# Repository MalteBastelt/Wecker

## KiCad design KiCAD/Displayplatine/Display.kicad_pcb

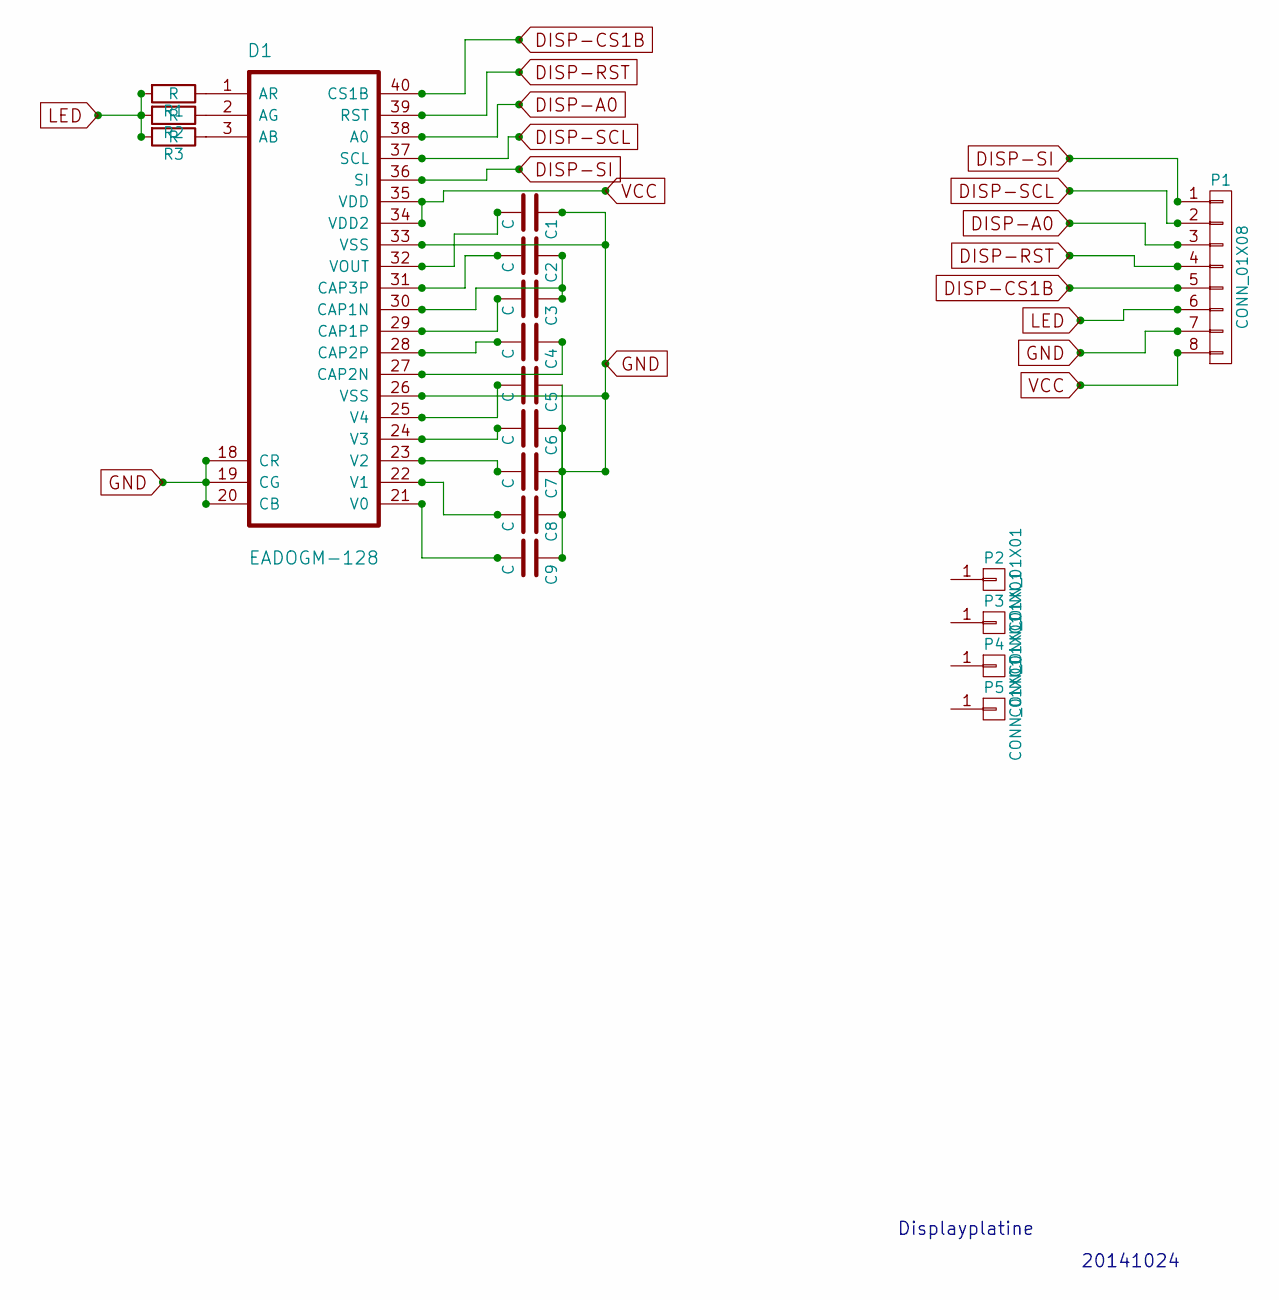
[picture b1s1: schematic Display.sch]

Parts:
C1, C2, C3, C4, C5, C6, C7, C8, C9: C; C_Disc_D7.5_P5
D1: EADOGM-128; EADOG128
P1: CONN_01X08; Pin_Header_Straight_1x08
P2, P3, P4, P5: CONN_01X01; Pin_Header_Straight_1x01
R1, R2, R3: R; Resistor_Horizontal_RM10mm

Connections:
D1: D1.36 (SI), P1.1
D2: D1.37 (SCL), P1.2
D3: D1.38 (A0), P1.3
D4: D1.39 (RST), P1.4
D5: D1.40 (CS1B), P1.5
GND: C1.1, C5.1, C6.1, C7.1, C8.1, C9.1, D1.18 (CR), D1.19 (CG), D1.20 (CB), D1.26 (VSS), D1.33 (VSS), P1.7
LED: P1.6, R1.2, R2.2, R3.2
unnamed: C1.2, D1.32 (VOUT)
unnamed: C2.1, C3.1, D1.30 (CAP1N)
unnamed: C2.2, D1.31 (CAP3P)
unnamed: C3.2, D1.29 (CAP1P)
unnamed: C4.1, D1.27 (CAP2N)
unnamed: C4.2, D1.28 (CAP2P)
unnamed: C5.2, D1.25 (V4)
unnamed: C6.2, D1.24 (V3)
unnamed: C7.2, D1.23 (V2)
unnamed: C8.2, D1.22 (V1)
unnamed: C9.2, D1.21 (V0)
unnamed: D1.1 (AR), R1.1
unnamed: D1.2 (AG), R2.1
unnamed: D1.3 (AB), R3.1
VCC: D1.34 (VDD2), D1.35 (VDD), P1.8

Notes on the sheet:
Displayplatine
20141024

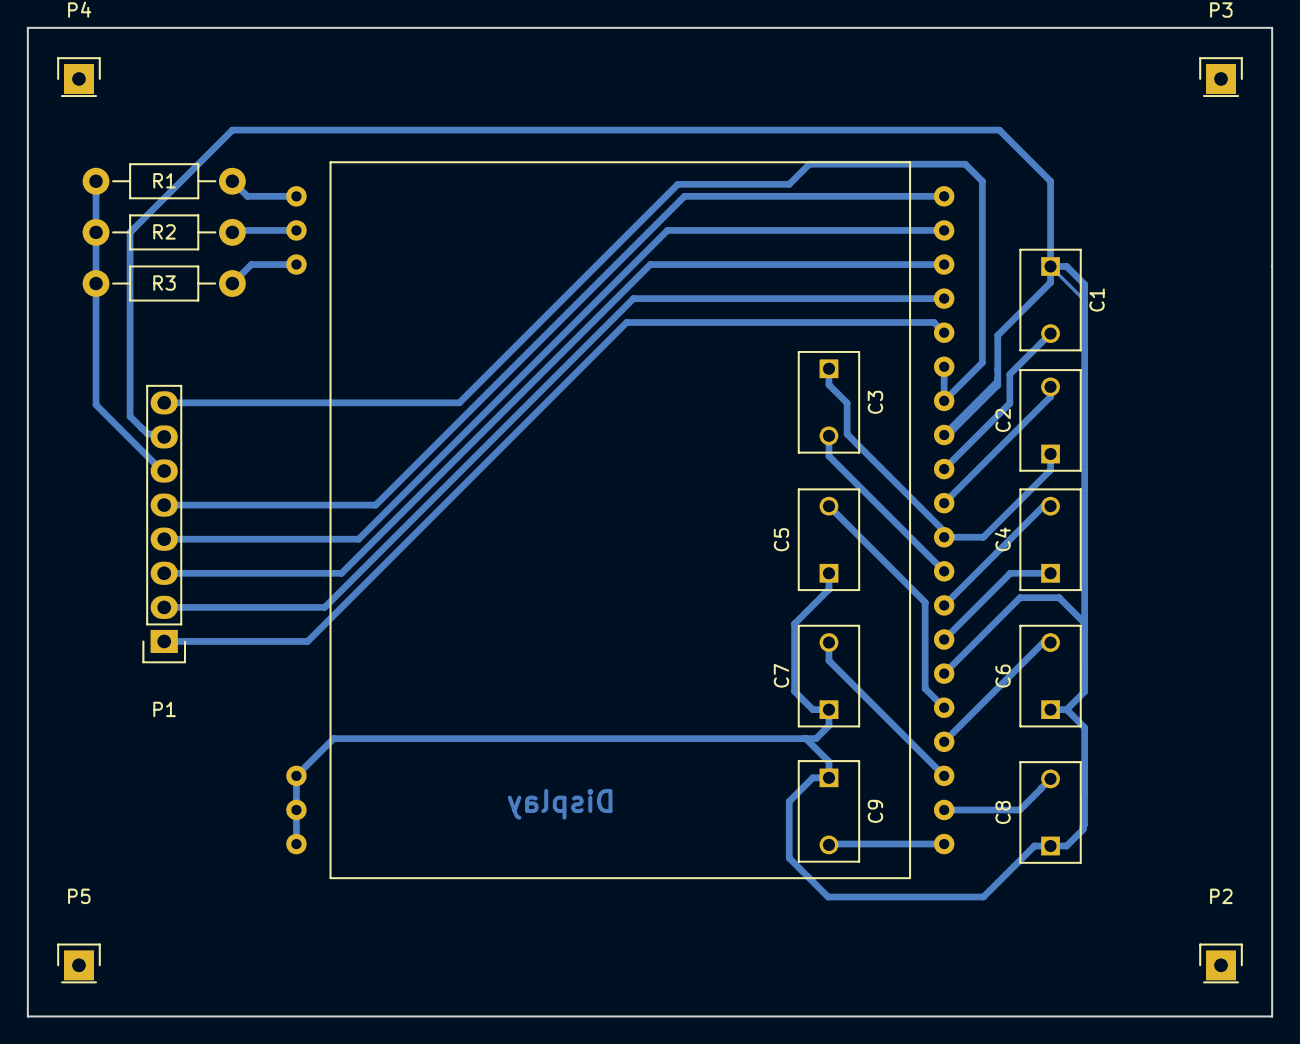
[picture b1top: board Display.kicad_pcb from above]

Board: 2 copper layers, 92.7 x 73.7 mm, 18 parts (0 on the bottom side), 22 nets.

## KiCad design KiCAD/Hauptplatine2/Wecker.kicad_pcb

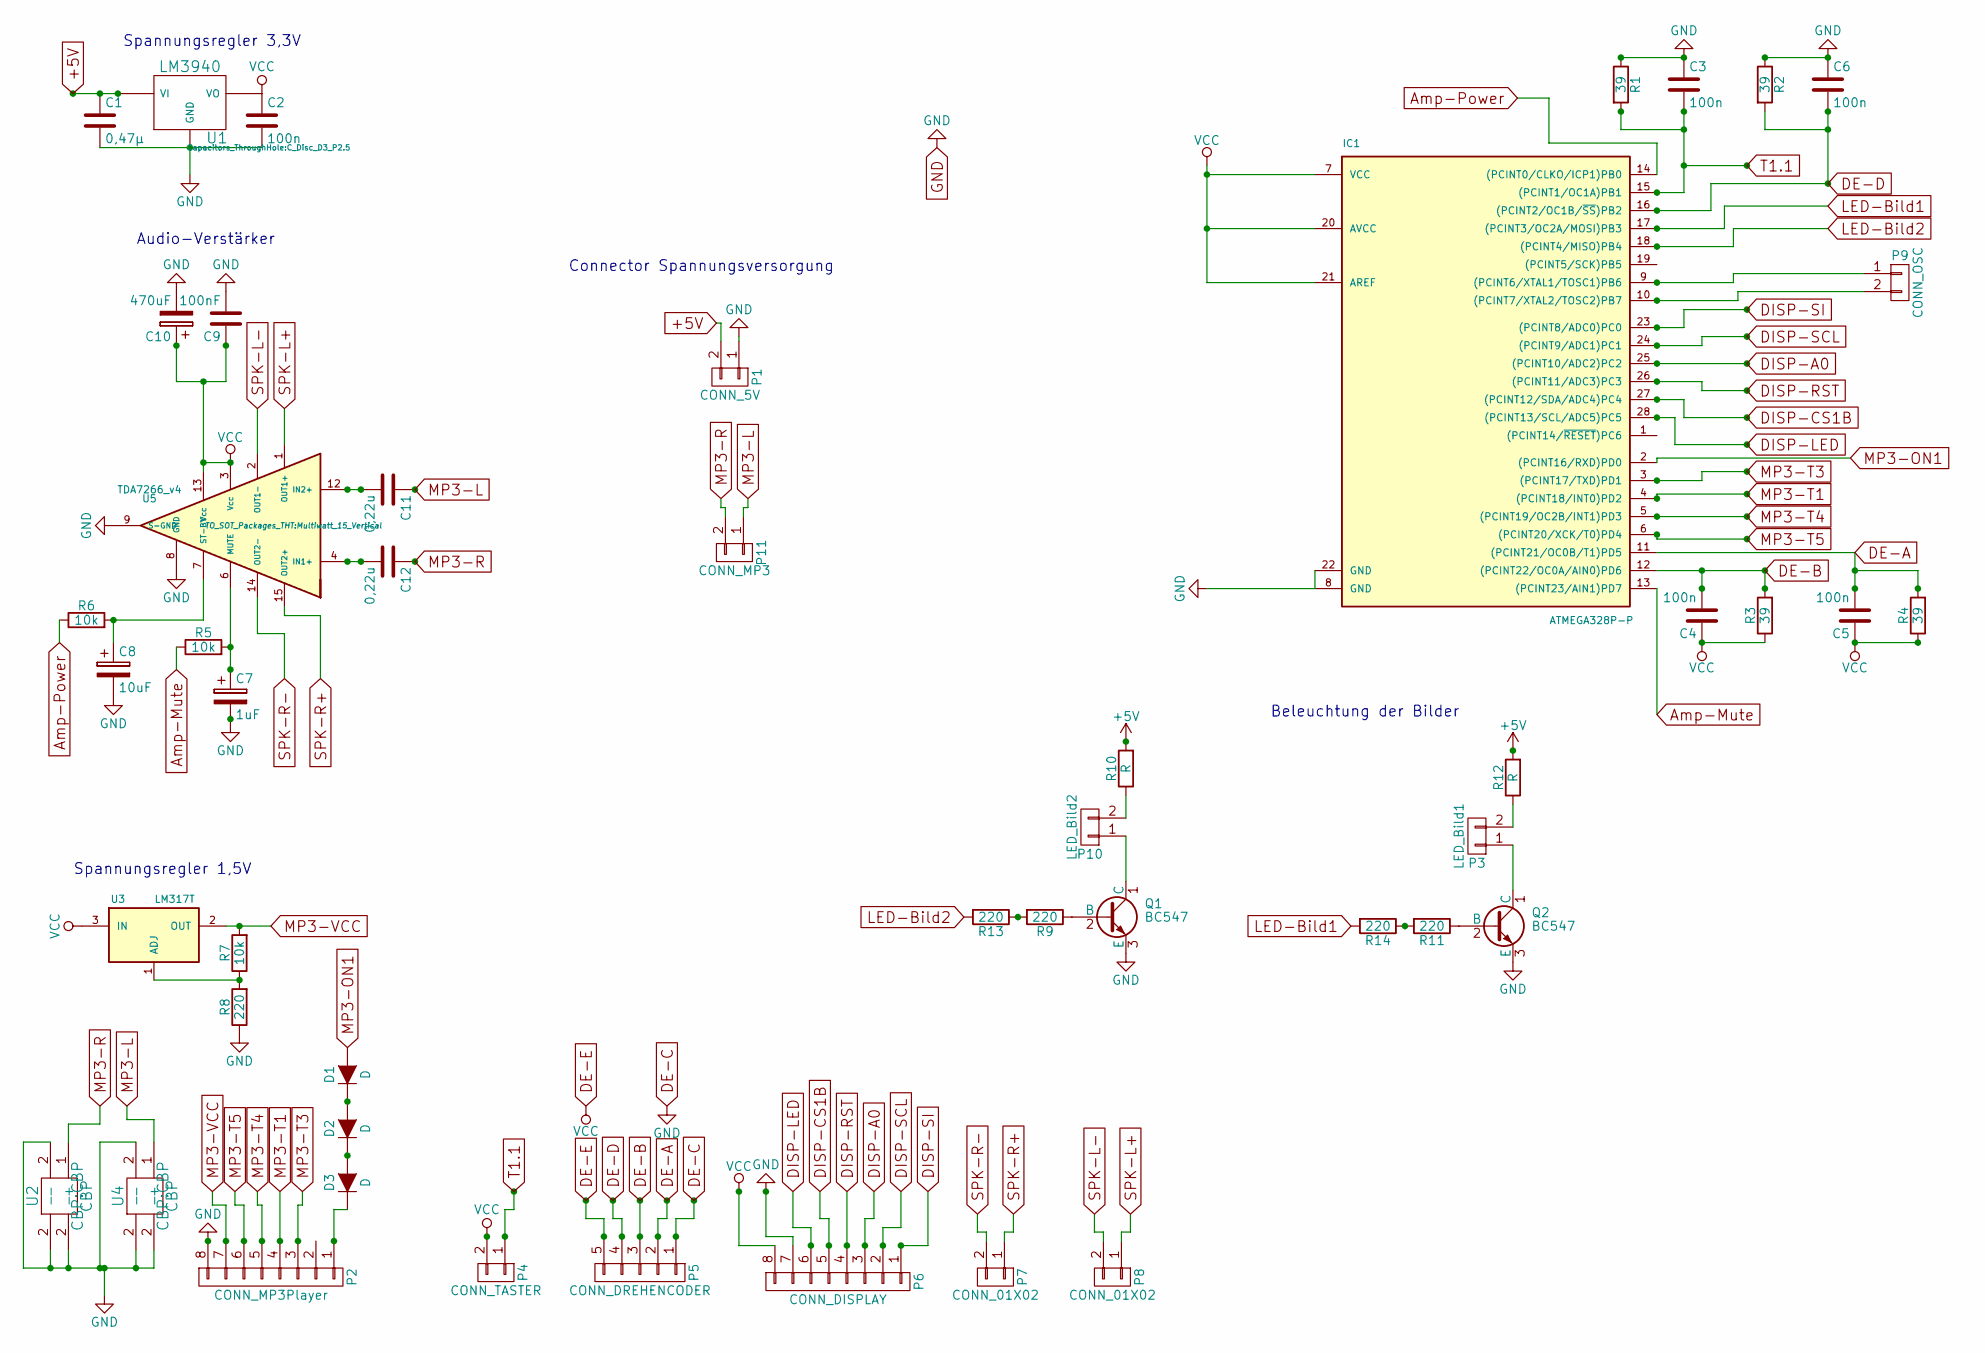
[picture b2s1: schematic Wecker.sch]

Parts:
C1: 0,47µ; C_Disc_D7.5_P5
C2: 100n; C_Disc_D3_P2.5
C3, C4, C5, C6: 100n; C_Disc_D12_P7.75
C7: 1uF; C_Radial_D5_L6_P2.5
C8: 10uF; C_Radial_D5_L6_P2.5
C9: 100nF; C_Disc_D12_P7.75
C10: 470uF; C_Radial_D7.5_L11.2_P2.5
C11, C12: 0,22u; C_Rect_L4_W2.5_P2.5
D1, D2, D3: D; Diode_DO-35_SOD27_Horizontal_RM10
IC1: ATMEGA328P-P; DIP-28_W7.62mm
P1: CONN_5V; PINHEAD1-2
P2: CONN_MP3Player; Wafer_Vertical22.5x5.8x7RM2.5-8
P3: LED_Bild1; PINHEAD1-2
P4: CONN_TASTER; PINHEAD1-2
P5: CONN_DREHENCODER; Wafer_Vertical15x5.8x7RM2.5-5
P6: CONN_DISPLAY; Wafer_Vertical22.5x5.8x7RM2.5-8
P7, P8: CONN_01X02; PINHEAD1-2
P9: CONN_OSC; Crystal_Round_Vertical_2mm
P10: LED_Bild2; PINHEAD1-2
P11: CONN_MP3; PINHEAD1-2
Q1, Q2: BC547; TO-92_Horizontal2_Inline_Narrow_Oval
R1, R2, R3, R4: 39; Resistor_Horizontal_RM10mm
R5, R6, R7: 10k; Resistor_Horizontal_RM15mm
R8, R9, R11, R13, R14: 220; Resistor_Horizontal_RM10mm
R10, R12: R; Resistor_Horizontal_RM10mm
U1: LM3940; TO-220
U2, U4: CBP
U3: LM317T; TO-220
U5: TDA7266_v4; Multiwatt_15_Vertical

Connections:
+5V: C1.1, P1.2, R10.2, R12.2, U1.1 (VI)
Amp-Mute: IC1.13 ((PCINT23/AIN1)PD7), R5.1
Amp-Power: IC1.14 ((PCINT0/CLKO/ICP1)PB0), R6.1
DE-A: C5.2, IC1.11 ((PCINT21/OC0B/T1)PD5), P5.2, R4.2
DE-B: C4.2, IC1.12 ((PCINT22/OC0A/AIN0)PD6), P5.3, R3.2
DE-C: C1.2, C2.2, C3.1, C6.1, C7.2, C8.2, C9.2, C10.2, IC1.8 (GND), IC1.22 (GND), P1.1, P2.8, P5.1, P6.7, Q1.3 (E), Q2.3 (E), R1.1, R2.1, R8.1, U1.2 (GND), U2.2 (-), U4.2 (-), U5.8 (GND), U5.9 (S-GND)
DE-D: C6.2, IC1.16 ((PCINT2/OC1B/~SS~)PB2), P5.4, R2.2
DE-E: C2.1, C4.1, C5.1, C9.1, C10.1, IC1.7 (VCC), IC1.20 (AVCC), IC1.21 (AREF), P4.2, P5.5, P6.8, R3.1, R4.1, U1.3 (VO), U3.3 (IN), U5.3 (Vcc), U5.13 (Vcc)
DISP-A0: IC1.25 ((PCINT10/ADC2)PC2), P6.3
DISP-CS1B: IC1.27 ((PCINT12/SDA/ADC4)PC4), P6.5
DISP-LED: IC1.28 ((PCINT13/SCL/ADC5)PC5), P6.6
DISP-RST: IC1.26 ((PCINT11/ADC3)PC3), P6.4
DISP-SCL: IC1.24 ((PCINT9/ADC1)PC1), P6.2
DISP-SI: IC1.23 ((PCINT8/ADC0)PC0), P6.1
LED-Bild1: IC1.17 ((PCINT3/OC2A/MOSI)PB3), R14.2
LED-Bild2: IC1.18 ((PCINT4/MISO)PB4), R13.2
MP3-L: C11.1, P11.1, U4.1 (+)
MP3-ON1: D1.2 (A), IC1.2 ((PCINT16/RXD)PD0)
MP3-R: C12.1, P11.2, U2.1 (+)
MP3-T1: IC1.4 ((PCINT18/INT0)PD2), P2.4
MP3-T3: IC1.3 ((PCINT17/TXD)PD1), P2.3
MP3-T4: IC1.5 ((PCINT19/OC2B/INT1)PD3), P2.5
MP3-T5: IC1.6 ((PCINT20/XCK/T0)PD4), P2.6
MP3-VCC: P2.7, R7.2, U3.2 (OUT)
unnamed: C7.1, R5.2, U5.6 (MUTE)
unnamed: C8.1, R6.2, U5.7 (ST-BY)
unnamed: C11.2, U5.12 (IN2+)
unnamed: C12.2, U5.4 (IN1+)
unnamed: D1.1 (K), D2.2 (A)
unnamed: D2.1 (K), D3.2 (A)
unnamed: D3.1 (K), P2.1
unnamed: IC1.9 ((PCINT6/XTAL1/TOSC1)PB6), P9.1
unnamed: IC1.10 ((PCINT7/XTAL2/TOSC2)PB7), P9.2
unnamed: P3.1, Q2.1 (C)
unnamed: P3.2, R12.1
unnamed: P10.1, Q1.1 (C)
unnamed: P10.2, R10.1
unnamed: Q1.2 (B), R9.1
unnamed: Q2.2 (B), R11.1
unnamed: R7.1, R8.2, U3.1 (ADJ)
unnamed: R11.2, R14.1
unnamed: R9.2, R13.1
SPK-L+: P8.1, U5.1 (OUT1+)
SPK-L-: P8.2, U5.2 (OUT1-)
SPK-R+: P7.1, U5.15 (OUT2+)
SPK-R-: P7.2, U5.14 (OUT2-)
T1.1: C3.2, IC1.15 ((PCINT1/OC1A)PB1), P4.1, R1.2

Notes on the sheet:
Spannungsregler 3,3V
Audio-Verstärker
Spannungsregler 1,5V
Connector Spannungsversorgung
Beleuchtung der Bilder

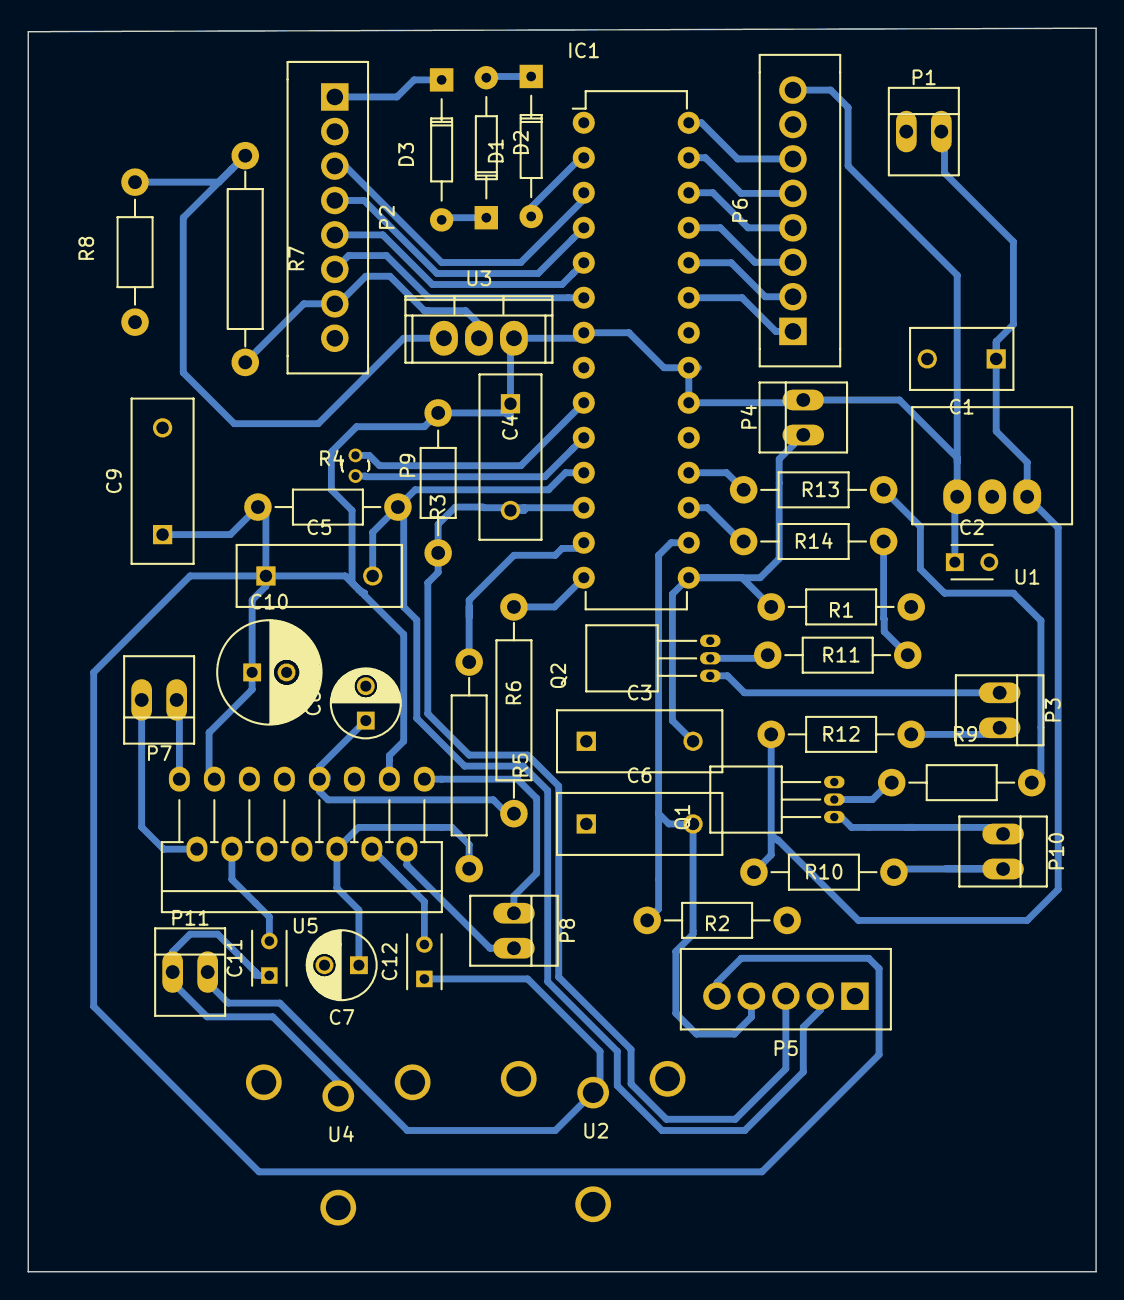
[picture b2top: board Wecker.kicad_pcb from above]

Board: 2 copper layers, 77.5 x 90.2 mm, 48 parts (0 on the bottom side), 47 nets.

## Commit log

2015-10-24 Platinenlayout ausprobiert
2015-10-24 Displayplatine Schematic erstellt
2015-10-24 Footprints auf Displayplatine zugeordnet
2015-10-24 Footprint EADOG korrigiert + Kondensatoren besserer Footprint
2015-10-24 Bauteile auf Displayplatine geordnet
2015-10-25 Displayplatine fertig + EADOG Footprint korrigiert
2015-10-28 nochmal
2015-10-28 Displayplatine fertig
2015-10-28 Hauptplatine inkl TDA7266
2015-11-11 Ordner 'Datenblätter' hinzugefügt
2015-11-11 Dokumentation hinzugefügt
2015-11-24 Doku_neu
2015-11-24 Submodule entfernt
2015-11-28 Layout Hauptplatine2 v1. Mp3Player-On falsch
2015-11-28 PCB enger gepackt. MP3 Player in Code eingebunden.
2015-11-28 Haupptlatine2 fertig, Masseflächen vergrößert, Leiterbahnen zusammengeschoben
2015-11-28 Doku: Transistorschaltung hinzugefügt
2015-11-29 alte Zeichnungen für Gehäuse entfernt
2015-11-29 Doku erweitert
2015-11-29 Front hinzugefügt
2015-12-03 Doku fortgesetzt, Platine wurde hergestellt
2015-12-12 Beleuchtung Plexiglas1 hinzugefügt
2015-12-17 Ports LED-Bilder korrigiert und Beleuchtung aktiviert; Aufweckfunktion fertiggestellt
2015-12-17 SnoozeLogo hinzugefügt + Alarm off wenn User wach ist
2015-12-21 snooze fix. mp3 wieder auf alten mp3-Player umgestellt.
2015-12-22 Finale
2016-01-14 Code: Weckzeit durch snooze verändern fixed. Doku erweitert.
2016-01-23 Literatur hinzugefügt
2016-01-23 Gehäuse + Fazit
